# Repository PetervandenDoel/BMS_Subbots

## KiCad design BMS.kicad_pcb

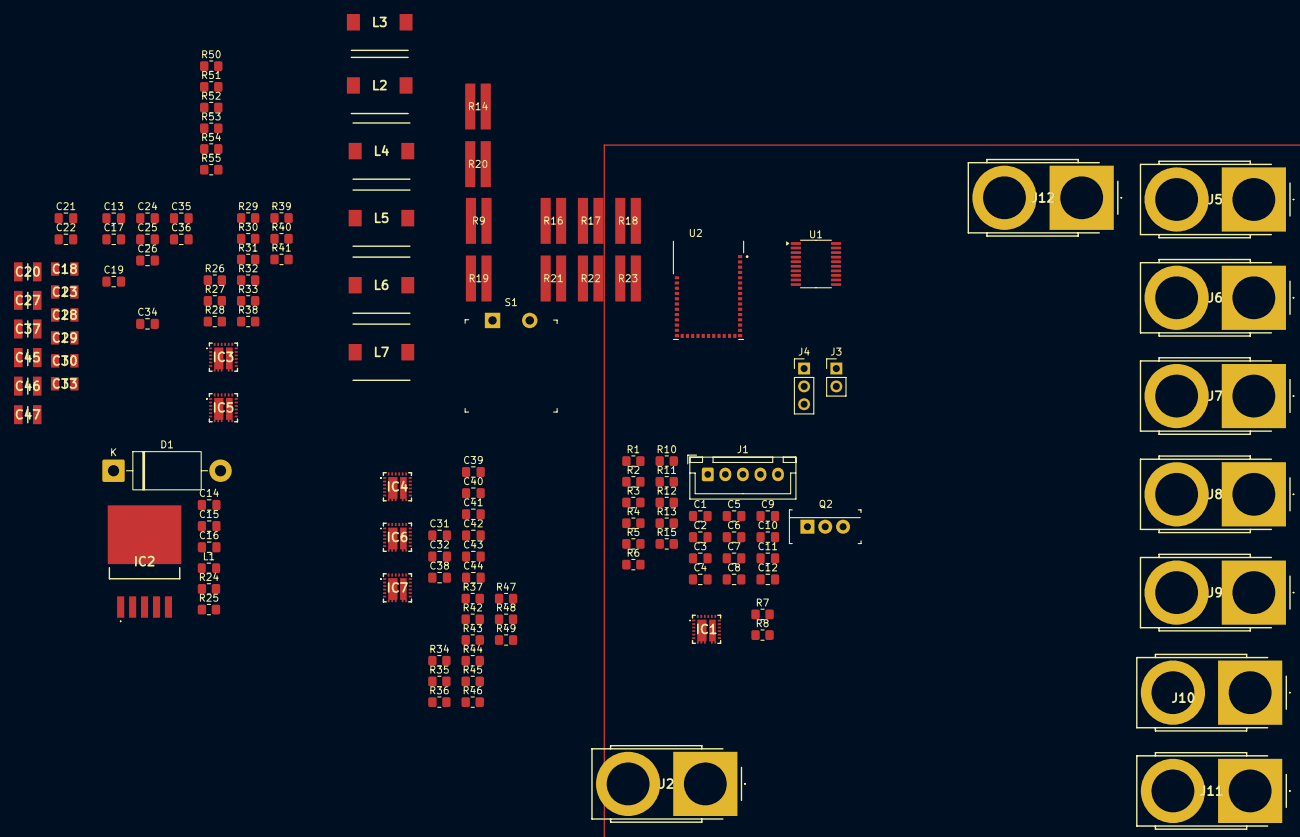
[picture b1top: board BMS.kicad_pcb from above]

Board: 2 copper layers, 133 parts (0 on the bottom side), 78 nets.

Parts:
C1, C2, C3, C4, C5, C6, C12: 1u; C_0805_2012Metric_Pad1.18x1.45mm_HandSolder
C7: 10u; C_0805_2012Metric_Pad1.18x1.45mm_HandSolder
C8, C9, C10, C19, C21, C24, C31, C32, C34, C38: 100n; C_0805_2012Metric_Pad1.18x1.45mm_HandSolder
C11, C17, C26, C36, C42, C43, C44: 4u7; C_0805_2012Metric_Pad1.18x1.45mm_HandSolder
C13, C16, C25, C35, C39, C40, C41: 10n; C_0805_2012Metric_Pad1.18x1.45mm_HandSolder
C14, C22: 100u; C_0805_2012Metric_Pad1.18x1.45mm_HandSolder
C15: 220u; C_0805_2012Metric_Pad1.18x1.45mm_HandSolder
C18, C23, C28, C29, C30, C33: TMK316BBJ226ML-T; CAPC3216X190N
C20, C27, C37, C45, C46, C47: EMK325ABJ107MM-P; CAPC3225X270N
D1: 1N5822; D_DO-201AD_P15.24mm_Horizontal
IC1, IC3, IC4, IC5, IC6, IC7: AOZ2261NQI-11; AOZ2261NQI11
IC2: LM2596DSADJG
J1: Conn_01x05_Pin; JST_XH_B5B-XH-A_1x05_P2.50mm_Vertical
J2, J5, J6, J7, J8, J9, J10, J11, J12: XT90PB-F; XT90PBF
J3: Conn_01x02_Pin; PinHeader_1x02_P2.54mm_Vertical
J4: Conn_01x03_Pin; PinHeader_1x03_P2.54mm_Vertical
L1: 33u; L_0805_2012Metric_Pad1.15x1.40mm_HandSolder
L2, L3, L4, L5, L6, L7: HCM1A0805-3R3-R; INDPM8180X540N
Q2: IRLB3813PBF; TO-220-3
R1, R2, R3, R4, R5, R6, R11, R12: 100; R_0805_2012Metric_Pad1.20x1.40mm_HandSolder
R7: 4k7'; R_0805_2012Metric_Pad1.20x1.40mm_HandSolder
R8, R15: 4k7; R_0805_2012Metric_Pad1.20x1.40mm_HandSolder
R9, R14, R16, R17, R18, R19, R20, R21, R22, R23: 13m; RES_LTR100L_ROM
R10: 1M; R_0805_2012Metric_Pad1.20x1.40mm_HandSolder
R13, R29, R33, R41, R45, R47, R49, R50, R51, R52, R53, R54, R55: 10k; R_0805_2012Metric_Pad1.20x1.40mm_HandSolder
R24: 3k1; R_0805_2012Metric_Pad1.20x1.40mm_HandSolder
R25: 1k; R_0805_2012Metric_Pad1.20x1.40mm_HandSolder
R26, R31, R37, R39, R42, R43: 100k; R_0805_2012Metric_Pad1.20x1.40mm_HandSolder
R27, R34: 1.2M; R_0805_2012Metric_Pad1.20x1.40mm_HandSolder
R28, R44: 190k; R_0805_2012Metric_Pad1.20x1.40mm_HandSolder
R30, R35: 600k; R_0805_2012Metric_Pad1.20x1.40mm_HandSolder
R32, R46: 140k; R_0805_2012Metric_Pad1.20x1.40mm_HandSolder
R36, R38: 333k; R_0805_2012Metric_Pad1.20x1.40mm_HandSolder
R40, R48: 75k; R_0805_2012Metric_Pad1.20x1.40mm_HandSolder
S1: GPTS203211B; PushButton_12x12mm_THT_GPTS203211B
U1: BQ76920PW; TSSOP-20_4.4x6.5mm_P0.65mm
U2: 453-00001R; XCVR_453-00001R

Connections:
5VOUT_A: C37.2, J12.2, L5.2, R40.2
5VOUT_B: C47.2, J11.2, L7.2, R48.2
9VOUT_A: C27.2, J9.2, L3.2, R32.2
9VOUT_B: C46.2, J10.2, L6.2, R46.2
12VOUT_A: C20.2, J7.2, L2.2, R28.2
12VOUT_B: C45.2, J8.2, L4.2, R44.2
+5V: C15.1, C16.2, C17.1, C26.1, C36.1, C42.1, C43.1, C44.1, IC1.21 (VCC), IC3.21 (VCC), IC4.21 (VCC), IC5.21 (VCC), IC6.21 (VCC), IC7.21 (VCC), L1.2, R24.2, R26.1, R31.1, R37.1, R39.1, R43.1
/ALERT: U1.20 (ALERT), U2.23 (P1.04/AIN0/CLK)
/PGOOD5_A: IC5.1 (PGOOD), R39.2
/PGOOD5_B: IC7.1 (PGOOD), R43.2
/PGOOD9_A: IC3.1 (PGOOD), R31.2
/PGOOD9_B: IC6.1 (PGOOD), R42.2
/PGOOD12_A: IC4.1 (PGOOD), R37.2
/PGOOD12_B: IC1.1 (PGOOD), R26.2
/Power Distribution/FB5_A: IC5.5 (FB), R40.1, R41.2
/Power Distribution/FB5_B: IC7.5 (FB), R48.1, R49.2
/Power Distribution/FB9_A: IC3.5 (FB), R32.1, R33.2
/Power Distribution/FB9_B: IC6.5 (FB), R46.1, R47.2
/Power Distribution/FB12_A: IC1.5 (FB), R28.1, R29.2
/Power Distribution/FB12_B: IC4.5 (FB), R44.1, R45.2
/Power Distribution/LX5_A: C34.1, IC5.10 (LX_1), IC5.11 (LX_2), IC5.16 (LX_3), IC5.17 (LX_4), IC5.18 (LX_5), IC5.25 (LX_6), L5.1
/Power Distribution/LX5_B: C38.1, IC7.10 (LX_1), IC7.11 (LX_2), IC7.16 (LX_3), IC7.17 (LX_4), IC7.18 (LX_5), IC7.25 (LX_6), L7.1
/Power Distribution/LX9_A: C24.1, IC3.10 (LX_1), IC3.11 (LX_2), IC3.16 (LX_3), IC3.17 (LX_4), IC3.18 (LX_5), IC3.25 (LX_6), L3.1
/Power Distribution/LX9_B: C32.1, IC6.10 (LX_1), IC6.11 (LX_2), IC6.16 (LX_3), IC6.17 (LX_4), IC6.18 (LX_5), IC6.25 (LX_6), L6.1
/Power Distribution/LX12_A: C19.1, IC1.10 (LX_1), IC1.11 (LX_2), IC1.16 (LX_3), IC1.17 (LX_4), IC1.18 (LX_5), IC1.25 (LX_6), L2.1
/Power Distribution/LX12_B: C31.1, IC4.10 (LX_1), IC4.11 (LX_2), IC4.16 (LX_3), IC4.17 (LX_4), IC4.18 (LX_5), IC4.25 (LX_6), L4.1
/Power Distribution/OCS5_A: IC5.19 (OCS), R52.2
/Power Distribution/OCS5_B: IC7.19 (OCS), R53.2
/Power Distribution/OCS9_A: IC3.19 (OCS), R51.2
/Power Distribution/OCS9_B: IC6.19 (OCS), R54.2
/Power Distribution/OCS12_A: IC1.19 (OCS), R50.2
/Power Distribution/OCS12_B: IC4.19 (OCS), R55.2
/REGOUT: C11.1, R7.1, R8.1, U1.8 (REGOUT), U2.26 (VDD_NRF)
/RegulatorInput/Feedback: C16.1, IC2.4 (FEEDBACK), R24.1, R25.1
/RegulatorInput/Output: D1.1 (K), IC2.2 (OUTPUT), L1.1
/SCL0: R8.2, U1.5 (SCL), U2.14 (P1.03/NFC2/CLK)
/SDA0: R7.2, U1.4 (SDA), U2.15 (P1.02/NFC1)
/SRN: C9.1, C10.1, R12.1, U1.19 (SRN)
/SRP: C8.1, C10.2, R11.1, U1.18 (SRP)
/SWDIO: J4.1, U2.5 (SWDIO)
/TS1: J3.1, R13.2, R15.1, U1.6 (TS1)
/VC0: R5.1, U1.17 (VC0)
/VC1: R4.1, S1.1, U1.16 (VC1)
/VC2: R3.1, U1.15 (VC2)
/VC3: R2.1, U1.13 (VC4), U1.14 (VC3)
/VC4: R1.1, U1.12 (VC5)
BAT+: C6.1, C14.1, C18.2, C21.1, C22.1, C23.2, C28.2, C29.2, C30.2, C33.2, IC1.7 (IN_1), IC1.8 (IN_2), IC1.9 (IN_3), IC1.22 (IN_4), IC1.24 (IN_5), IC2.1 (VIN), IC3.7 (IN_1), IC3.8 (IN_2), IC3.9 (IN_3), IC3.22 (IN_4), IC3.24 (IN_5), IC4.7 (IN_1), IC4.8 (IN_2), IC4.9 (IN_3), IC4.22 (IN_4), IC4.24 (IN_5), IC5.7 (IN_1), IC5.8 (IN_2), IC5.9 (IN_3), IC5.22 (IN_4), IC5.24 (IN_5), IC6.7 (IN_1), IC6.8 (IN_2), IC6.9 (IN_3), IC6.22 (IN_4), IC6.24 (IN_5), IC7.7 (IN_1), IC7.8 (IN_2), IC7.9 (IN_3), IC7.22 (IN_4), IC7.24 (IN_5), J2.2, J5.2, J6.2, R6.1, R27.2, R30.2, R34.2, R35.2, R36.2, R38.2, U1.9 (REGSRC)
BAT-: C4.2, C5.1, C5.2, C6.2, C7.2, C8.2, C9.2, C11.2, C12.2, C21.2, C22.2, J1.1, J2.1, R5.2, R9.2, R11.2, R14.2, R16.2, R17.2, R18.2, R19.2, R20.2, R21.2, R22.2, R23.2, U1.3 (VSS)
GNDA: C13.2, C17.2, C25.2, C26.2, C35.2, C36.2, C39.2, C40.2, C41.2, C42.2, C43.2, C44.2, IC1.3 (MODE), IC1.4 (AGND), IC3.3 (MODE), IC3.4 (AGND), IC4.3 (MODE), IC4.4 (AGND), IC5.3 (MODE), IC5.4 (AGND), IC6.3 (MODE), IC6.4 (AGND), IC7.3 (MODE), IC7.4 (AGND), R29.1, R33.1, R41.1, R45.1, R47.1, R49.1, R50.1, R51.1, R52.1, R53.1, R54.1, R55.1
GNDPWR: C18.1, C20.1, C23.1, C27.1, C28.1, C29.1, C30.1, C33.1, C37.1, C45.1, C46.1, C47.1, IC1.12 (PGND_1), IC1.13 (PGND_2), IC1.14 (PGND_3), IC1.15 (PGND_4), IC3.12 (PGND_1), IC3.13 (PGND_2), IC3.14 (PGND_3), IC3.15 (PGND_4), IC4.12 (PGND_1), IC4.13 (PGND_2), IC4.14 (PGND_3), IC4.15 (PGND_4), IC5.12 (PGND_1), IC5.13 (PGND_2), IC5.14 (PGND_3), IC5.15 (PGND_4), IC6.12 (PGND_1), IC6.13 (PGND_2), IC6.14 (PGND_3), IC6.15 (PGND_4), IC7.12 (PGND_1), IC7.13 (PGND_2), IC7.14 (PGND_3), IC7.15 (PGND_4)
unnamed: C19.2, IC1.20 (BST)
unnamed: C13.1, IC1.23 (SS)
unnamed: IC1.6 (TON), R27.1
unnamed: C24.2, IC3.20 (BST)
unnamed: C25.1, IC3.23 (SS)
unnamed: IC3.6 (TON), R30.1
unnamed: C31.2, IC4.20 (BST)
unnamed: C39.1, IC4.23 (SS)
unnamed: IC4.6 (TON), R34.1
unnamed: C34.2, IC5.20 (BST)
unnamed: C35.1, IC5.23 (SS)
unnamed: IC5.6 (TON), R38.1
unnamed: C32.2, IC6.20 (BST)
unnamed: C40.1, IC6.23 (SS)
unnamed: IC6.6 (TON), R35.1
unnamed: C38.2, IC7.20 (BST)
unnamed: C41.1, IC7.23 (SS)
unnamed: IC7.6 (TON), R36.1
unnamed: C3.2, C4.1, J1.2, R4.2
unnamed: C2.2, C3.1, J1.3, R3.2
unnamed: C1.2, C2.1, J1.4, R2.2
unnamed: C1.1, J1.5, R1.2
unnamed: Q2.1 (G), R10.1, U1.1 (DSG)
unnamed: Q2.3 (S), R9.1, R10.2, R12.2, R14.1, R16.1, R17.1, R18.1, R19.1, R20.1, R21.1, R22.1, R23.1
unnamed: R13.1, S1.2
unnamed: C7.1, R6.2, U1.10 (BAT)
unnamed: C12.1, U1.7 (CAP1)
PACK-: C14.2, C15.2, D1.2 (A), IC2.3 (GROUND_1), IC2.5 (~ON/OFF), IC2.6 (GROUND_2), J3.2, J4.3, J5.1, J6.1, J7.1, J8.1, J9.1, J10.1, J11.1, J12.1, Q2.2 (D), R15.2, R25.2, U2.1 (GND), U2.16 (GND), U2.27 (GND), U2.39 (GND)

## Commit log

2025-12-22 PrePeter
2026-01-05 Test commit
2026-01-08 Added 3.3u inductors to schematic and PCB file, created project specific library folder and added inductor model to it
2026-01-08 Added output and input caps for buck converters into the schematic. Added components into the project specific library.
2026-01-09 Changed RTon values to get reasonable osscilation frequencies for all the buck converters, added 10K current limit resistors to all the OCS pins, adjusted some net names to be different for the two b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
2026-01-09 Added A and Bonto the all the net labels and sheet outputs for the pairs of buck converters. Moved the XT90 connector for the battery input to the connectors sectionof the main sheet and renamed the 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
2026-01-09 Added note to change the ground of the Nordic MCU to the battery minus terminal rather than the ground of the rest of the sub. The power to the nordic won't be measured by coulomb counting, but I arg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
2026-01-09 Added EN and Pgood pins for the second set of buck converters to the NRF
2026-01-25 dealing with merge issues
